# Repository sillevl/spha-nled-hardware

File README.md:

# SPHA NLED hardware

SPHA LED-related board/module.

## Design files

- `spha-NLED.kicad_pro` — KiCad project
- `spha-NLED.kicad_sch` — top-level schematic
- `spha-NLED.kicad_pcb` — PCB layout

## Working with the project

Open the `.kicad_pro` file in KiCad. The design includes files originating from an older KiCad workflow; review schematic links, footprints, design rules, zones, and manufacturing outputs after any conversion or upgrade.

KiCad source files and project-specific libraries are the source of truth. Generated BOM, Gerber, assembly, and fabrication-house outputs are excluded from the repository; regenerate and verify them before manufacturing.

## Repository notes

Temporary KiCad state, locks, autosaves, and backup directories are excluded by `.gitignore`. Board revision, tested KiCad version, manufacturing revision, and hardware/firmware compatibility still need to be recorded when provenance is confirmed.

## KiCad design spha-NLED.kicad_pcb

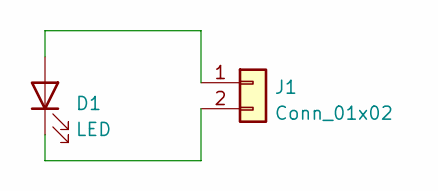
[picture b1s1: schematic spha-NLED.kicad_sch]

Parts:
D1: LED; LED_D3.0mm
J1: Conn_01x02; PinSocket_1x02_P2.54mm_Vertical

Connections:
unnamed: D1.1 (K), J1.2
unnamed: D1.2 (A), J1.1

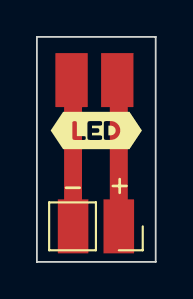
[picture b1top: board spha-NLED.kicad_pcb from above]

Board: 2 copper layers, 6.6 x 12.5 mm, 3 parts (0 on the bottom side), 2 nets.

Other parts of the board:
kibuzzard-63B2BD5D: G***; kibuzzard-63B2BD5D
